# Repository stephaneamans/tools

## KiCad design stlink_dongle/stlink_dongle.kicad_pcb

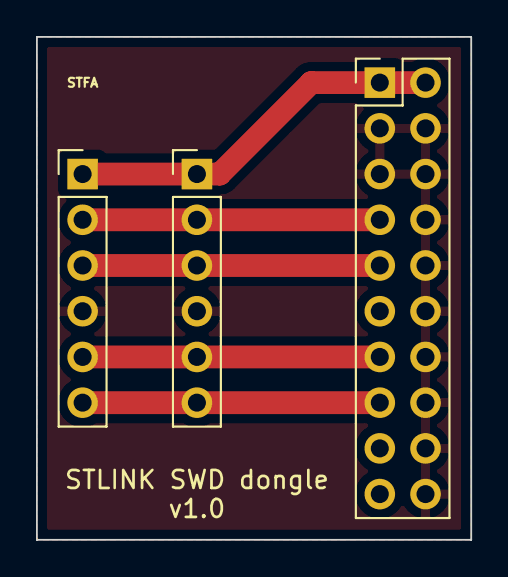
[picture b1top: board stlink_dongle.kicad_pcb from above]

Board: 2 copper layers, 24.1 x 27.9 mm, 3 parts (0 on the bottom side), 6 nets.

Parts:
J1: Conn_HE13_1x6_2.54V; PinHeader_1x06_P2.54mm_Vertical
J2: dnp; PinHeader_1x06_P2.54mm_Vertical
J3: Conn_HE13_2x10_2.54V; PinHeader_2x10_P2.54mm_Vertical

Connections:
/nrst: J1.6, J2.6, J3.15
/swd_clk: J1.3, J2.3, J3.9
/swd_io: J1.2, J2.2, J3.7
/target_vdd: J1.1, J2.1, J3.1, J3.2
/traceswo: J1.5, J2.5, J3.13
GND: J1.4, J2.4, J3.3, J3.4, J3.5, J3.6, J3.8, J3.10, J3.12, J3.14, J3.16, J3.18, J3.20

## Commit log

2021-08-09 Hardware STLINK SWD dongle
